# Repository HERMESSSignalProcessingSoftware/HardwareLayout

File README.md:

# HardwareLayout

## To consider for iteration 3.1
- [X] Rename 5V-28V to 5V-noniso
- [X] STAMP labeling
- [X] Northmarking Top and Bottom
- [X] Far fewer power LEDs
- [X] PTH LEDs via ZE05
- [ ] Label LEDs on PCB
- [X] Strip LED resistor network
- [X] LED Renames: LED_FPGA_LOADED(#13), LED_HB_MEMSYNC(#16), LED_HB_MSS(#14), LED_RECORDING(#15)
- [X] Strip 0 and inf valued devices
- [X] Inverting RXSM Connector
- [X] LM4030 for SGR measurement
- [X] VCCINT auf 1.2V
- [X] Bank0 und Bank6 auf 1.2V und connections an Spannung anpassen
- [X] Optocoupling Pullups
- [X] Main Clk for SF2
- [X] Fix broken Flash package
- [X] Replace FT2232D with FT2232H
- [X] (discarded) FTDI 1MOhm beim Oszi?
- [X] (discarded) FTDI Pins 3 42 und Ende R9 an 5V statt 3V3
- [X] (discarded) FTDI SI/WU auf 3V3

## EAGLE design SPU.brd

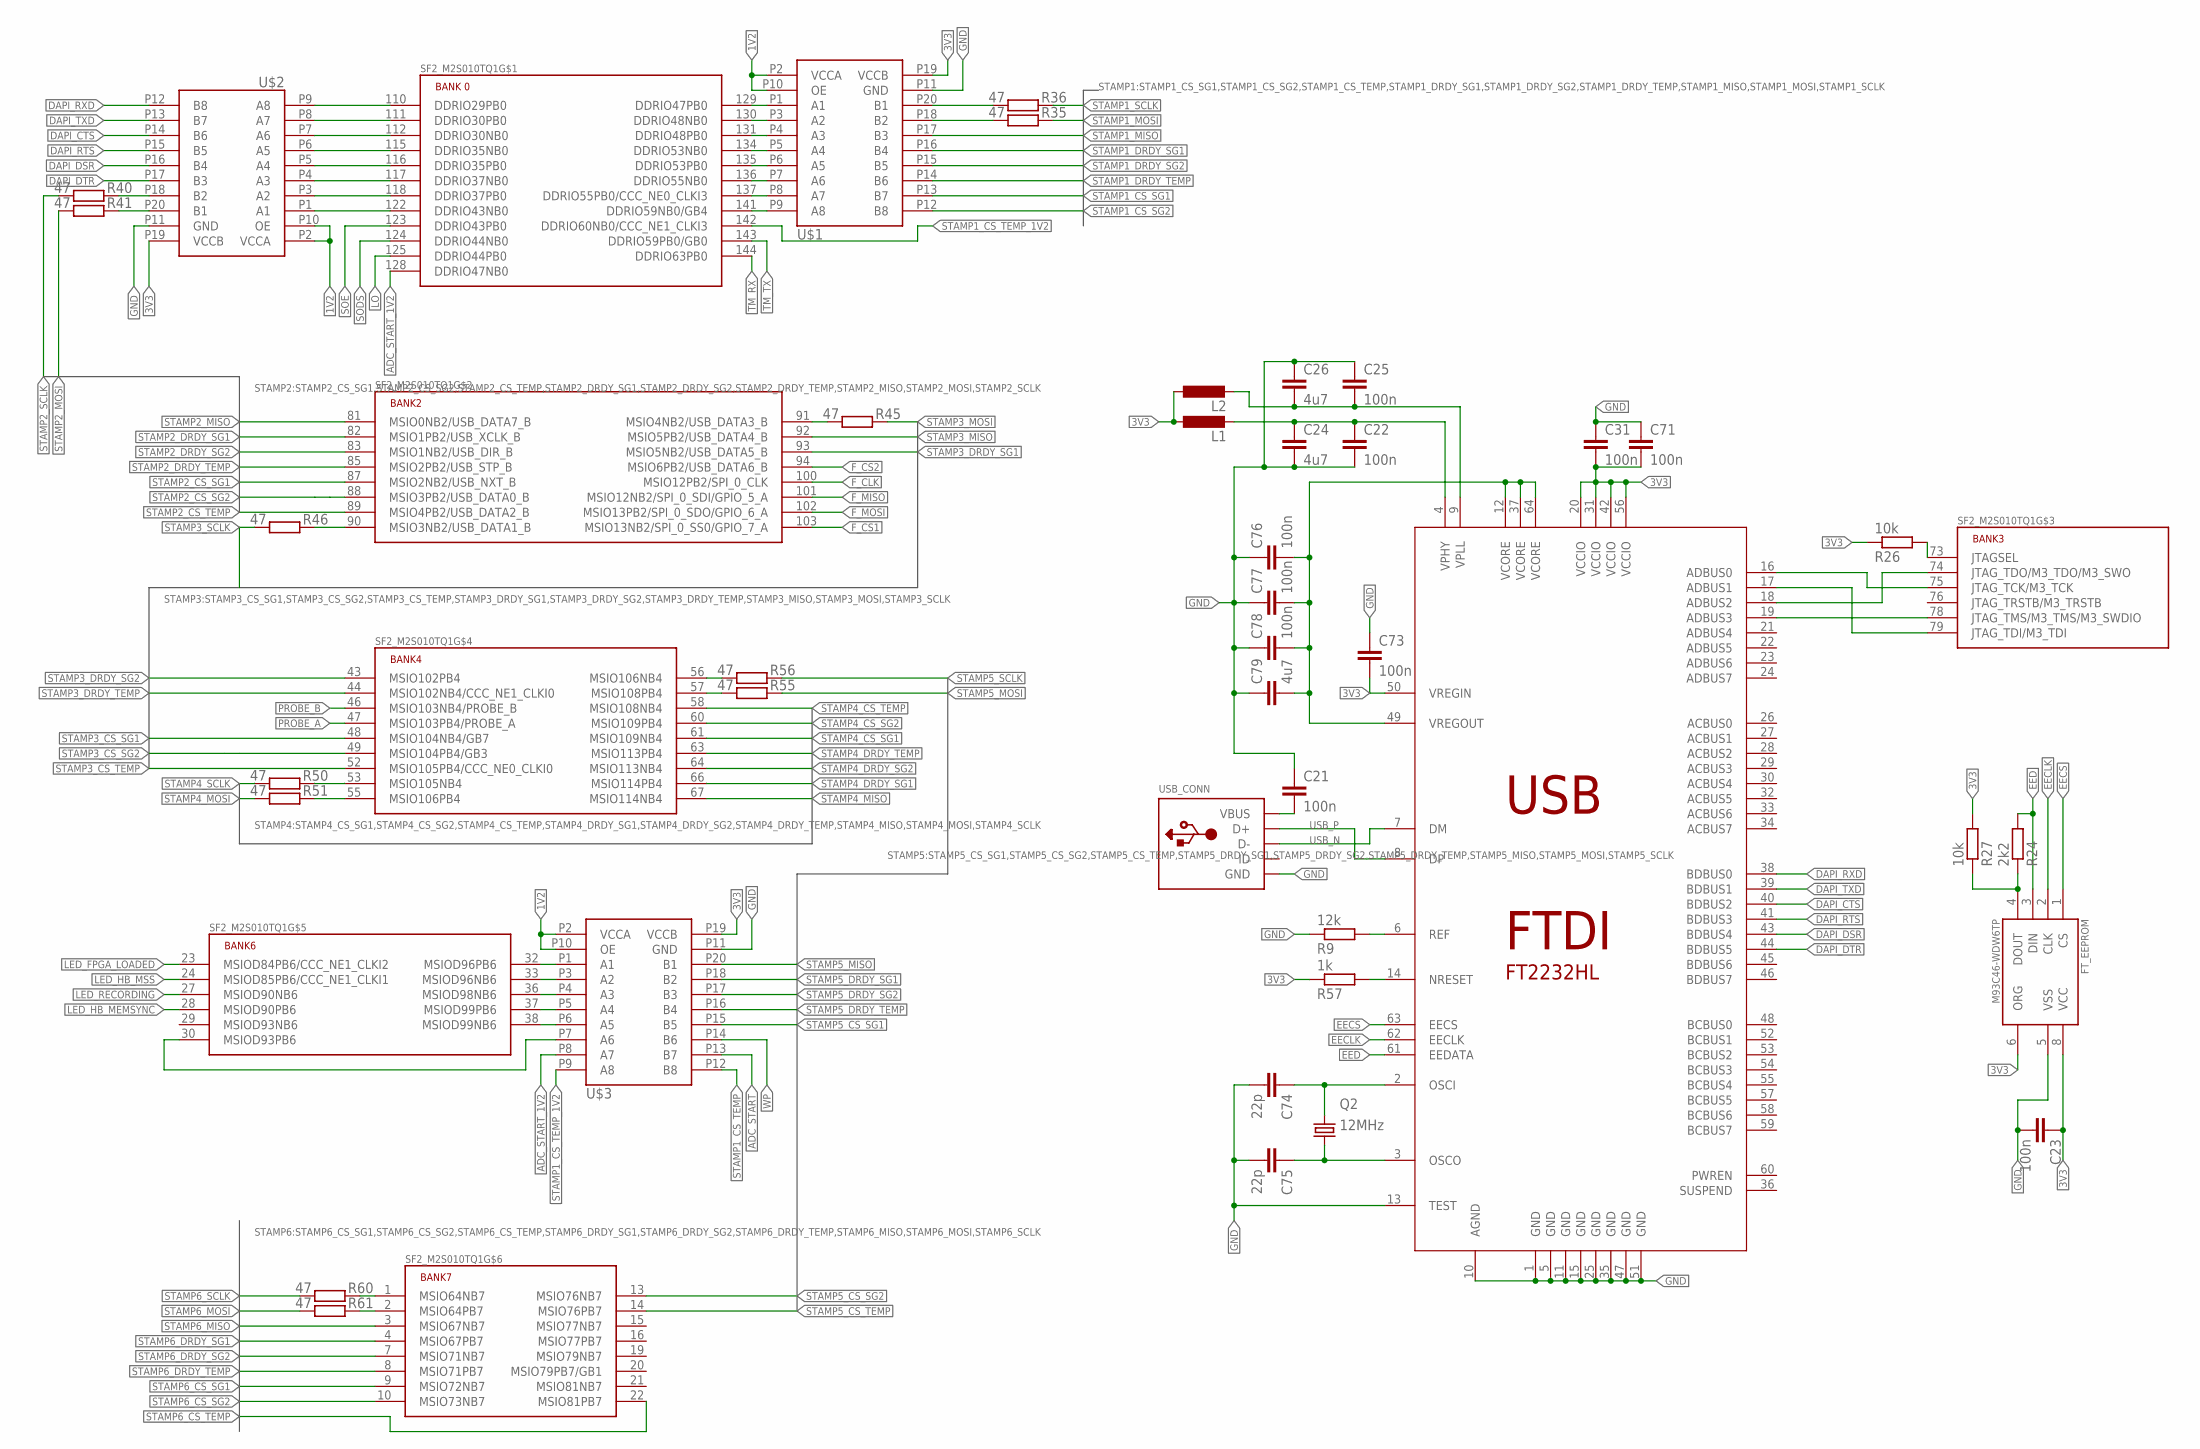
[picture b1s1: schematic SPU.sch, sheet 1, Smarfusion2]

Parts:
C21, C22, C23, C25, C31, C71, C73, C76, C77, C78: 100n; C0805
C24, C26, C79: 4u7; C0805
C74, C75: 22p; C0805
FT_EEPROM: M93C46-WDW6TP; TSSOP-8
L1, L2: L-EUL1812; L1812
Q2: 12MHz; HC49UP
R9: 12k; R0805
R24: 2k2; R0805
R26, R27: 10k; R0805
R35, R36, R40, R41, R45, R46, R50, R51, R55, R56, R60, R61: 47; R0805
R57: 1k; R0805
SF2_M2S010TQ1: SF2_M2S010TQ144; TQFP144
U$1, U$2, U$3: NXB0108PWJ; TSSOP-20
USB: FT2232HL; LQFP64
USB_CONN: USBMINIB; USB-MINIB

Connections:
1V2: U$1.P2 (VCCA), U$1.P10 (OE), U$2.P2 (VCCA), U$2.P10 (OE), U$3.P2 (VCCA), U$3.P10 (OE); also elsewhere on the board
3V3: C23.1, C31.2, C71.2, C73.2, FT_EEPROM.6 (ORG), FT_EEPROM.8 (VCC), L1.1, L2.1, R26.1, R27.2, R57.1, U$1.P19 (VCCB), U$2.P19 (VCCB), U$3.P19 (VCCB), USB.20 (VCCIO), USB.31 (VCCIO), USB.42 (VCCIO), USB.50 (VREGIN), USB.56 (VCCIO); also elsewhere on the board
ADC_START: U$3.P13 (B7); also elsewhere on the board
ADC_START_1V2: SF2_M2S010TQ1.128 (DDRIO47NB0), U$3.P8 (A7)
DAPI_CTS: U$2.P14 (B6), USB.40 (BDBUS2)
DAPI_DSR: U$2.P16 (B4), USB.43 (BDBUS4)
DAPI_DTR: U$2.P17 (B3), USB.44 (BDBUS5)
DAPI_RTS: U$2.P15 (B5), USB.41 (BDBUS3)
DAPI_RXD: U$2.P12 (B8), USB.38 (BDBUS0)
DAPI_TXD: U$2.P13 (B7), USB.39 (BDBUS1)
EECLK: FT_EEPROM.2 (CLK), USB.62 (EECLK)
EECS: FT_EEPROM.1 (CS), USB.63 (EECS)
EED: FT_EEPROM.3 (DIN), R24.2, USB.61 (EEDATA)
F_CLK: SF2_M2S010TQ1.100 (MSIO12PB2/SPI_0_CLK); also elsewhere on the board
F_CS1: SF2_M2S010TQ1.103 (MSIO13NB2/SPI_0_SS0/GPIO_7_A); also elsewhere on the board
F_CS2: SF2_M2S010TQ1.94 (MSIO6PB2/USB_DATA6_B); also elsewhere on the board
F_MISO: SF2_M2S010TQ1.101 (MSIO12NB2/SPI_0_SDI/GPIO_5_A); also elsewhere on the board
F_MOSI: SF2_M2S010TQ1.102 (MSIO13PB2/SPI_0_SDO/GPIO_6_A); also elsewhere on the board
GND: C21.1, C22.2, C23.2, C24.2, C25.1, C26.1, C31.1, C71.1, C73.1, C74.2, C75.2, C76.1, C77.1, C78.1, C79.1, FT_EEPROM.5 (VSS), R9.1, U$1.P11 (GND), U$2.P11 (GND), U$3.P11 (GND), USB.1 (GND), USB.5 (GND), USB.10 (AGND), USB.11 (GND), USB.13 (TEST), USB.15 (GND), USB.25 (GND), USB.35 (GND), USB.47 (GND), USB.51 (GND), USB_CONN.GND; also elsewhere on the board
LED_FPGA_LOADED: SF2_M2S010TQ1.23 (MSIOD84PB6/CCC_NE1_CLKI2); also elsewhere on the board
LED_HB_MEMSYNC: SF2_M2S010TQ1.28 (MSIOD90PB6); also elsewhere on the board
LED_HB_MSS: SF2_M2S010TQ1.24 (MSIOD85PB6/CCC_NE1_CLKI1); also elsewhere on the board
LED_RECORDING: SF2_M2S010TQ1.27 (MSIOD90NB6); also elsewhere on the board
LO: SF2_M2S010TQ1.125 (DDRIO44PB0); also elsewhere on the board
unnamed: R26.2, SF2_M2S010TQ1.73 (JTAGSEL)
unnamed: C74.1, Q2.2, USB.2 (OSCI)
unnamed: SF2_M2S010TQ1.32 (MSIOD96PB6), U$3.P1 (A1)
unnamed: SF2_M2S010TQ1.33 (MSIOD96NB6), U$3.P3 (A2)
unnamed: SF2_M2S010TQ1.36 (MSIOD98NB6), U$3.P4 (A3)
unnamed: C21.2, USB_CONN.VBUS
unnamed: C22.1, C24.1, L1.2, USB.4 (VPHY)
unnamed: R36.2, U$1.P20 (B1)
unnamed: SF2_M2S010TQ1.75 (JTAG_TCK/M3_TCK), USB.16 (ADBUS0)
unnamed: SF2_M2S010TQ1.79 (JTAG_TDI/M3_TDI), USB.17 (ADBUS1)
unnamed: SF2_M2S010TQ1.74 (JTAG_TDO/M3_TDO/M3_SWO), USB.18 (ADBUS2)
unnamed: SF2_M2S010TQ1.78 (JTAG_TMS/M3_TMS/M3_SWDIO), USB.19 (ADBUS3)
unnamed: SF2_M2S010TQ1.37 (MSIOD99PB6), U$3.P5 (A4)
unnamed: FT_EEPROM.4 (DOUT), R24.1, R27.1
unnamed: R35.2, U$1.P18 (B2)
unnamed: SF2_M2S010TQ1.118 (DDRIO37PB0), U$2.P3 (A2)
unnamed: SF2_M2S010TQ1.122 (DDRIO43NB0), U$2.P1 (A1)
unnamed: R40.1, U$2.P18 (B2)
unnamed: SF2_M2S010TQ1.129 (DDRIO47PB0), U$1.P1 (A1)
unnamed: R41.1, U$2.P20 (B1)
unnamed: R46.1, SF2_M2S010TQ1.90 (MSIO3NB2/USB_DATA1_B)
unnamed: R45.2, SF2_M2S010TQ1.91 (MSIO4NB2/USB_DATA3_B)
unnamed: SF2_M2S010TQ1.130 (DDRIO48NB0), U$1.P3 (A2)
unnamed: SF2_M2S010TQ1.131 (DDRIO48PB0), U$1.P4 (A3)
unnamed: SF2_M2S010TQ1.134 (DDRIO53NB0), U$1.P5 (A4)
unnamed: SF2_M2S010TQ1.135 (DDRIO53PB0), U$1.P6 (A5)
unnamed: SF2_M2S010TQ1.136 (DDRIO55NB0), U$1.P7 (A6)
unnamed: SF2_M2S010TQ1.137 (DDRIO55PB0/CCC_NE0_CLKI3), U$1.P8 (A7)
unnamed: SF2_M2S010TQ1.141 (DDRIO59NB0/GB4), U$1.P9 (A8)
unnamed: SF2_M2S010TQ1.38 (MSIOD99NB6), U$3.P6 (A5)
unnamed: SF2_M2S010TQ1.110 (DDRIO29PB0), U$2.P9 (A8)
unnamed: SF2_M2S010TQ1.111 (DDRIO30PB0), U$2.P8 (A7)
unnamed: SF2_M2S010TQ1.112 (DDRIO30NB0), U$2.P7 (A6)
unnamed: SF2_M2S010TQ1.115 (DDRIO35NB0), U$2.P6 (A5)
unnamed: R50.1, SF2_M2S010TQ1.53 (MSIO105NB4)
unnamed: R51.1, SF2_M2S010TQ1.55 (MSIO106PB4)
unnamed: SF2_M2S010TQ1.116 (DDRIO35PB0), U$2.P5 (A4)
unnamed: SF2_M2S010TQ1.117 (DDRIO37NB0), U$2.P4 (A3)
unnamed: SF2_M2S010TQ1.30 (MSIOD93PB6), U$3.P7 (A6)
unnamed: R55.2, SF2_M2S010TQ1.57 (MSIO108PB4)
unnamed: R56.2, SF2_M2S010TQ1.56 (MSIO106NB4)
unnamed: R60.1, SF2_M2S010TQ1.1 (MSIO64NB7)
unnamed: R61.1, SF2_M2S010TQ1.2 (MSIO64PB7)
unnamed: R57.2, USB.14 (NRESET)
unnamed: R9.2, USB.6 (REF)
unnamed: C75.1, Q2.1, USB.3 (OSCO)
unnamed: C76.2, C77.2, C78.2, C79.2, USB.12 (VCORE), USB.37 (VCORE), USB.49 (VREGOUT), USB.64 (VCORE)
unnamed: C25.2, C26.2, L2.2, USB.9 (VPLL)
PROBE_A: SF2_M2S010TQ1.47 (MSIO103PB4/PROBE_A); also elsewhere on the board
PROBE_B: SF2_M2S010TQ1.46 (MSIO103NB4/PROBE_B); also elsewhere on the board
SODS: SF2_M2S010TQ1.124 (DDRIO44NB0); also elsewhere on the board
SOE: SF2_M2S010TQ1.123 (DDRIO43PB0); also elsewhere on the board
STAMP1_CS_SG1: U$1.P13 (B7); also elsewhere on the board
STAMP1_CS_SG2: U$1.P12 (B8); also elsewhere on the board
STAMP1_CS_TEMP: U$3.P12 (B8); also elsewhere on the board
STAMP1_CS_TEMP_1V2: SF2_M2S010TQ1.142 (DDRIO60NB0/CCC_NE1_CLKI3), U$3.P9 (A8)
STAMP1_DRDY_SG1: U$1.P16 (B4); also elsewhere on the board
STAMP1_DRDY_SG2: U$1.P15 (B5); also elsewhere on the board
STAMP1_DRDY_TEMP: U$1.P14 (B6); also elsewhere on the board
STAMP1_MISO: U$1.P17 (B3); also elsewhere on the board
STAMP1_MOSI: R35.1; also elsewhere on the board
STAMP1_SCLK: R36.1; also elsewhere on the board
STAMP2_CS_SG1: SF2_M2S010TQ1.87 (MSIO2NB2/USB_NXT_B); also elsewhere on the board
STAMP2_CS_SG2: SF2_M2S010TQ1.88 (MSIO3PB2/USB_DATA0_B); also elsewhere on the board
STAMP2_CS_TEMP: SF2_M2S010TQ1.89 (MSIO4PB2/USB_DATA2_B); also elsewhere on the board
STAMP2_DRDY_SG1: SF2_M2S010TQ1.82 (MSIO1PB2/USB_XCLK_B); also elsewhere on the board
STAMP2_DRDY_SG2: SF2_M2S010TQ1.83 (MSIO1NB2/USB_DIR_B); also elsewhere on the board
STAMP2_DRDY_TEMP: SF2_M2S010TQ1.85 (MSIO2PB2/USB_STP_B); also elsewhere on the board
STAMP2_MISO: SF2_M2S010TQ1.81 (MSIO0NB2/USB_DATA7_B); also elsewhere on the board
STAMP2_MOSI: R41.2; also elsewhere on the board
STAMP2_SCLK: R40.2; also elsewhere on the board
STAMP3_CS_SG1: SF2_M2S010TQ1.48 (MSIO104NB4/GB7); also elsewhere on the board
STAMP3_CS_SG2: SF2_M2S010TQ1.49 (MSIO104PB4/GB3); also elsewhere on the board
STAMP3_CS_TEMP: SF2_M2S010TQ1.52 (MSIO105PB4/CCC_NE0_CLKI0); also elsewhere on the board
STAMP3_DRDY_SG1: SF2_M2S010TQ1.93 (MSIO5NB2/USB_DATA5_B); also elsewhere on the board
STAMP3_DRDY_SG2: SF2_M2S010TQ1.43 (MSIO102PB4); also elsewhere on the board
STAMP3_DRDY_TEMP: SF2_M2S010TQ1.44 (MSIO102NB4/CCC_NE1_CLKI0); also elsewhere on the board
STAMP3_MISO: SF2_M2S010TQ1.92 (MSIO5PB2/USB_DATA4_B); also elsewhere on the board
STAMP3_MOSI: R45.1; also elsewhere on the board
STAMP3_SCLK: R46.2; also elsewhere on the board
STAMP4_CS_SG1: SF2_M2S010TQ1.61 (MSIO109NB4); also elsewhere on the board
STAMP4_CS_SG2: SF2_M2S010TQ1.60 (MSIO109PB4); also elsewhere on the board
STAMP4_CS_TEMP: SF2_M2S010TQ1.58 (MSIO108NB4); also elsewhere on the board
STAMP4_DRDY_SG1: SF2_M2S010TQ1.66 (MSIO114PB4); also elsewhere on the board
STAMP4_DRDY_SG2: SF2_M2S010TQ1.64 (MSIO113NB4); also elsewhere on the board
STAMP4_DRDY_TEMP: SF2_M2S010TQ1.63 (MSIO113PB4); also elsewhere on the board
STAMP4_MISO: SF2_M2S010TQ1.67 (MSIO114NB4); also elsewhere on the board
STAMP4_MOSI: R51.2; also elsewhere on the board
STAMP4_SCLK: R50.2; also elsewhere on the board
STAMP5_CS_SG1: U$3.P15 (B5); also elsewhere on the board
STAMP5_CS_SG2: SF2_M2S010TQ1.13 (MSIO76NB7); also elsewhere on the board
STAMP5_CS_TEMP: SF2_M2S010TQ1.14 (MSIO76PB7); also elsewhere on the board
STAMP5_DRDY_SG1: U$3.P18 (B2); also elsewhere on the board
STAMP5_DRDY_SG2: U$3.P17 (B3); also elsewhere on the board
STAMP5_DRDY_TEMP: U$3.P16 (B4); also elsewhere on the board
STAMP5_MISO: U$3.P20 (B1); also elsewhere on the board
STAMP5_MOSI: R55.1; also elsewhere on the board
STAMP5_SCLK: R56.1; also elsewhere on the board
STAMP6_CS_SG1: SF2_M2S010TQ1.9 (MSIO72NB7); also elsewhere on the board
STAMP6_CS_SG2: SF2_M2S010TQ1.10 (MSIO73NB7); also elsewhere on the board
STAMP6_CS_TEMP: SF2_M2S010TQ1.22 (MSIO81PB7); also elsewhere on the board
STAMP6_DRDY_SG1: SF2_M2S010TQ1.4 (MSIO67PB7); also elsewhere on the board
STAMP6_DRDY_SG2: SF2_M2S010TQ1.7 (MSIO71NB7); also elsewhere on the board
STAMP6_DRDY_TEMP: SF2_M2S010TQ1.8 (MSIO71PB7); also elsewhere on the board
STAMP6_MISO: SF2_M2S010TQ1.3 (MSIO67NB7); also elsewhere on the board
STAMP6_MOSI: R61.2; also elsewhere on the board
STAMP6_SCLK: R60.2; also elsewhere on the board
TM_RX: SF2_M2S010TQ1.144 (DDRIO63PB0); also elsewhere on the board
TM_TX: SF2_M2S010TQ1.143 (DDRIO59PB0/GB0); also elsewhere on the board
USB_N: USB.7 (DM), USB_CONN.D-
USB_P: USB.8 (DP), USB_CONN.D+
WP: U$3.P14 (B6); also elsewhere on the board

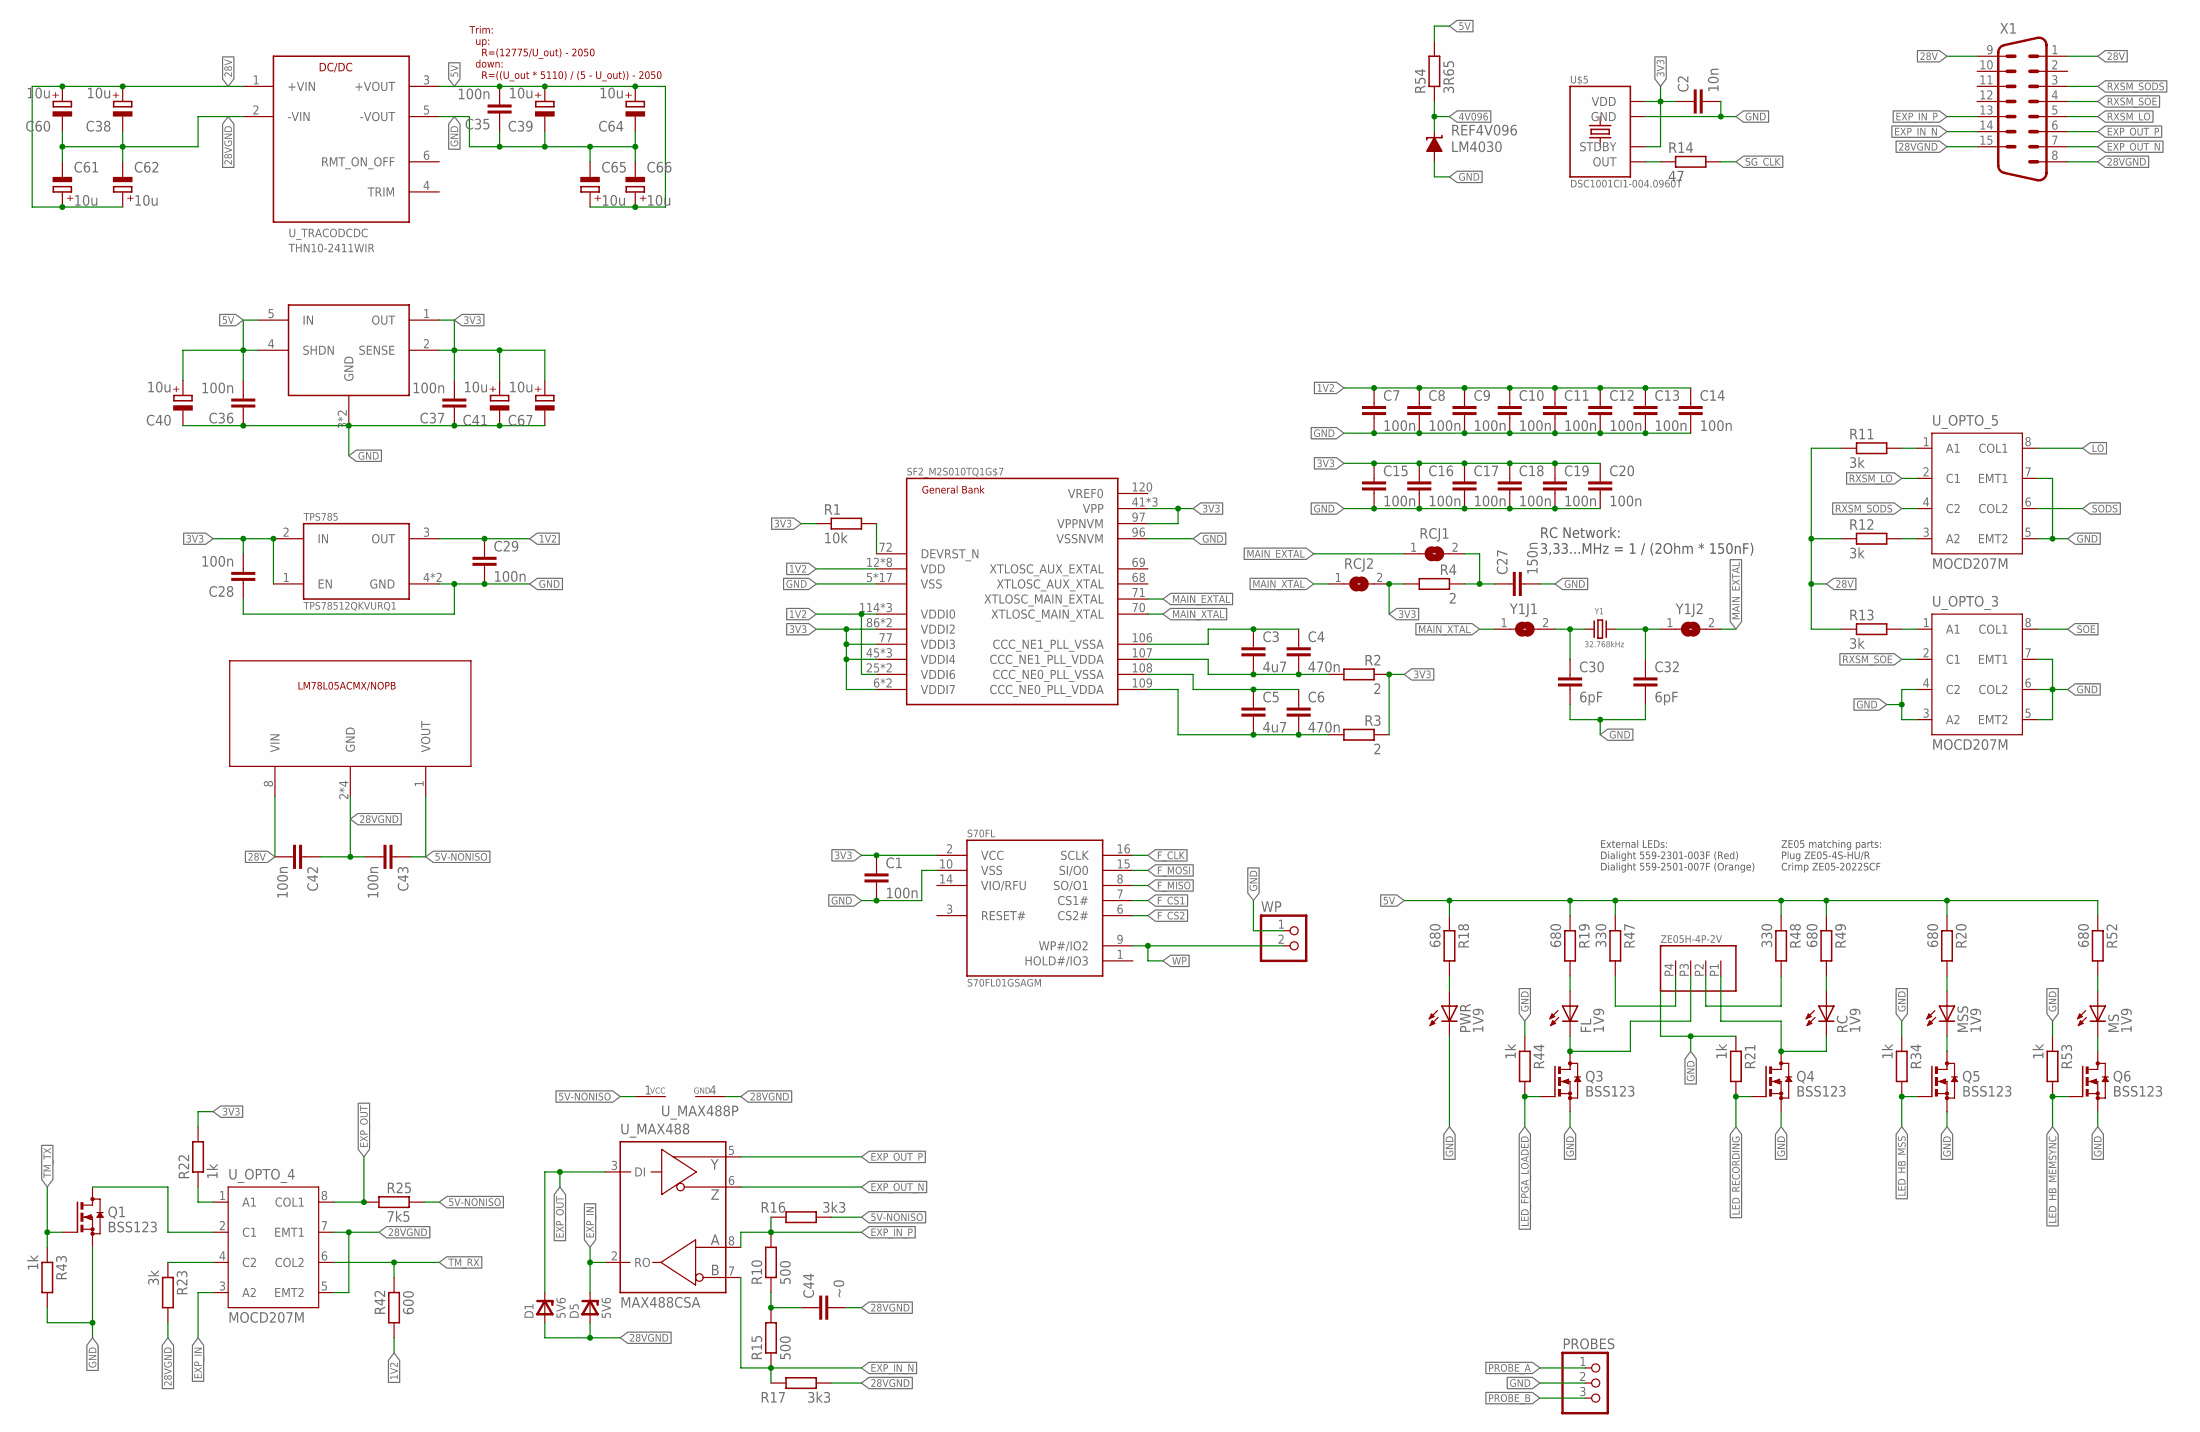
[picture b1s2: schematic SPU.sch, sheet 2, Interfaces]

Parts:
C1, C7, C8, C9, C10, C11, C12, C13, C14, C15, C16, C17, C18, C19, C20, C28, C29, C35, C36, C37, C43: 100n; C0805
C2: 10n; C0805
C3, C5: 4u7; C0805
C4, C6: 470n; C0805
C27: 150n; C0805
C30, C32: 6pF; C0805
C38, C39, C40, C41, C60, C61, C62, C64, C65, C66, C67: 10u; E/7260-38W
C42: 100n; C1206
C44: ~0; C0805
D1, D5: 5V6; DMELF
FL: 1V9; CHIP-LED0805
MS: 1V9; CHIP-LED0805
MSS: 1V9; CHIP-LED0805
PROBES: PSS254_G3
PWR: 1V9; CHIP-LED0805
Q1, Q3, Q4, Q5, Q6: BSS123; SOT23
R1: 10k; R0805
R2, R3, R4: 2; R0805
R10, R15: 500; R0805
R11, R12, R13, R23: 3k; R0805
R14: 47; R0805
R16, R17: 3k3; R0805
R18, R19, R20, R49, R52: 680; R0805
R21, R22, R34, R43, R44, R53: 1k; R0805
R25: 7k5; R0805
R42: 600; R0805
R47, R48: 330; R0805
R54: 3R65; R0805
RC: 1V9; CHIP-LED0805
RCJ1, RCJ2: SJ
REF4V096: LM4030; SOT-23
S70FL: S70FL01GSAGM; SOIC16
SF2_M2S010TQ1: SF2_M2S010TQ144; TQFP144
TPS78512QKVURQ1: TPS785; TO-252-5
U$5: DSC1001CI1-004.0960T; CDFN3225
U_7805: LM78L05ACMX/NOPB; SOIC8
U_LT1528: LT1528; Q5-DD
U_MAX488: MAX488CSA; SO08
U_OPTO_3, U_OPTO_4, U_OPTO_5: MOCD207M; SOIC127P594X363-8N
U_TRACODCDC: THN10-2411WIR; THL_20WI_SERIES
WP: PSS254_G2
X1: M15H
Y1: 32.768kHz; WE-XTAL_IQXC-90
Y1J1, Y1J2: SJ
ZE05H-4P-2V: ZE05-4P-2V; ZE05H-4P-2V

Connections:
1V2: C7.1, C8.1, C9.1, C10.1, C11.1, C12.1, C13.1, C14.1, C29.1, R42.1, SF2_M2S010TQ1.12 (VDD), SF2_M2S010TQ1.25 (VDDI6), SF2_M2S010TQ1.31 (VDD), SF2_M2S010TQ1.35 (VDDI6), SF2_M2S010TQ1.39 (VDD), SF2_M2S010TQ1.50 (VDD), SF2_M2S010TQ1.95 (VDD), SF2_M2S010TQ1.105 (VDD), SF2_M2S010TQ1.114 (VDDI0), SF2_M2S010TQ1.121 (VDD), SF2_M2S010TQ1.127 (VDDI0), SF2_M2S010TQ1.133 (VDD), SF2_M2S010TQ1.138 (VDDI0), TPS78512QKVURQ1.3 (OUT); also elsewhere on the board
3V3: C1.1, C2.1, C15.1, C16.1, C17.1, C18.1, C19.1, C20.1, C28.2, C37.2, C41.+, C67.+, R1.1, R2.1, R3.1, R4.2, R22.2, RCJ2.2, S70FL.2 (VCC), SF2_M2S010TQ1.6 (VDDI7), SF2_M2S010TQ1.17 (VDDI7), SF2_M2S010TQ1.41 (VPP), SF2_M2S010TQ1.45 (VDDI4), SF2_M2S010TQ1.54 (VDDI4), SF2_M2S010TQ1.62 (VDDI4), SF2_M2S010TQ1.77 (VDDI3), SF2_M2S010TQ1.80 (VPP), SF2_M2S010TQ1.86 (VDDI2), SF2_M2S010TQ1.97 (VPPNVM), SF2_M2S010TQ1.99 (VDDI2), SF2_M2S010TQ1.104 (VPP), TPS78512QKVURQ1.1 (EN), TPS78512QKVURQ1.2 (IN), U$5.P1 (STDBY), U$5.P4 (VDD), U_LT1528.1 (OUT), U_LT1528.2 (SENSE); also elsewhere on the board
4V096: R54.1, REF4V096.P4 (C); also elsewhere on the board
5V: C35.2, C36.2, C39.+, C40.+, C64.+, C65.+, C66.+, R18.1, R19.1, R20.1, R47.1, R48.1, R49.1, R52.1, R54.2, U_LT1528.4 (SHDN), U_LT1528.5 (IN), U_TRACODCDC.3 (+VOUT)
5V-NONISO: C43.1, R16.1, R25.2, U_7805.1 (VOUT), U_MAX488.1 (VCC)
28V: C38.+, C42.2, C60.+, C61.+, C62.+, R11.1, R12.1, R13.1, U_7805.8 (VIN), U_TRACODCDC.1 (+VIN), X1.1, X1.9
28VGND: C38.-, C42.1, C43.2, C44.2, C60.-, C61.-, C62.-, D1.A, D5.A, R17.1, R23.2, U_7805.2 (GND), U_7805.3 (GND), U_7805.6 (GND), U_7805.7 (GND), U_MAX488.4 (GND), U_OPTO_4.5 (EMT2), U_OPTO_4.7 (EMT1), U_TRACODCDC.2 (-VIN), X1.8, X1.15
EXP_IN: D5.C, U_MAX488.2 (RO), U_OPTO_4.3 (A2)
EXP_IN_N: R15.1, R17.2, U_MAX488.7 (B), X1.14
EXP_IN_P: R10.2, R16.2, U_MAX488.8 (A), X1.13
EXP_OUT: D1.C, R25.1, U_MAX488.3 (DI), U_OPTO_4.8 (COL1)
EXP_OUT_N: U_MAX488.6 (Z), X1.7
EXP_OUT_P: U_MAX488.5 (Y), X1.6
F_CLK: S70FL.16 (SCLK); also elsewhere on the board
F_CS1: S70FL.7 (CS1#); also elsewhere on the board
F_CS2: S70FL.6 (CS2#); also elsewhere on the board
F_MISO: S70FL.8 (SO/O1); also elsewhere on the board
F_MOSI: S70FL.15 (SI/O0); also elsewhere on the board
GND: C1.2, C2.2, C7.2, C8.2, C9.2, C10.2, C11.2, C12.2, C13.2, C14.2, C15.2, C16.2, C17.2, C18.2, C19.2, C20.2, C27.2, C28.1, C29.2, C30.2, C32.2, C35.1, C36.1, C37.1, C39.-, C40.-, C41.-, C64.-, C65.-, C66.-, C67.-, PROBES.2, PWR.C, Q1.2 (S), Q3.2 (S), Q4.2 (S), Q5.2 (S), Q6.2 (S), R21.1, R34.1, R43.2, R44.1, R53.1, REF4V096.P5 (A), S70FL.10 (VSS), SF2_M2S010TQ1.5 (VSS), SF2_M2S010TQ1.11 (VSS), SF2_M2S010TQ1.18 (VSS), SF2_M2S010TQ1.26 (VSS), SF2_M2S010TQ1.34 (VSS), SF2_M2S010TQ1.40 (VSS), SF2_M2S010TQ1.42 (VSS), SF2_M2S010TQ1.51 (VSS), SF2_M2S010TQ1.59 (VSS), SF2_M2S010TQ1.65 (VSS), SF2_M2S010TQ1.84 (VSS), SF2_M2S010TQ1.96 (VSSNVM), SF2_M2S010TQ1.98 (VSS), SF2_M2S010TQ1.113 (VSS), SF2_M2S010TQ1.119 (VSS), SF2_M2S010TQ1.126 (VSS), SF2_M2S010TQ1.132 (VSS), SF2_M2S010TQ1.139 (VSS), TPS78512QKVURQ1.4 (GND), TPS78512QKVURQ1.5 (GND), U$5.P2 (GND), U_LT1528.3 (GND), U_LT1528.6 (GND), U_OPTO_3.3 (A2), U_OPTO_3.4 (C2), U_OPTO_3.5 (EMT2), U_OPTO_3.6 (COL2), U_OPTO_3.7 (EMT1), U_OPTO_5.5 (EMT2), U_OPTO_5.7 (EMT1), U_TRACODCDC.5 (-VOUT), WP.1, ZE05H-4P-2V.P5, ZE05H-4P-2V.P6; also elsewhere on the board
LED_FPGA_LOADED: Q3.1 (G), R44.2; also elsewhere on the board
LED_HB_MEMSYNC: Q6.1 (G), R53.2; also elsewhere on the board
LED_HB_MSS: Q5.1 (G), R34.2; also elsewhere on the board
LED_RECORDING: Q4.1 (G), R21.2; also elsewhere on the board
LO: U_OPTO_5.8 (COL1); also elsewhere on the board
MAIN_EXTAL: RCJ1.1, SF2_M2S010TQ1.71 (XTLOSC_MAIN_EXTAL), Y1J2.2
MAIN_XTAL: RCJ2.1, SF2_M2S010TQ1.70 (XTLOSC_MAIN_XTAL), Y1J1.1
unnamed: C44.1, R10.1, R15.2
unnamed: R1.2, SF2_M2S010TQ1.72 (DEVRST_N)
unnamed: R23.1, U_OPTO_4.4 (C2)
unnamed: C3.1, C4.1, SF2_M2S010TQ1.106 (CCC_NE1_PLL_VSSA)
unnamed: C3.2, C4.2, R2.2, SF2_M2S010TQ1.107 (CCC_NE1_PLL_VDDA)
unnamed: C5.2, C6.2, R3.2, SF2_M2S010TQ1.109 (CCC_NE0_PLL_VDDA)
unnamed: C5.1, C6.1, SF2_M2S010TQ1.108 (CCC_NE0_PLL_VSSA)
unnamed: C30.1, Y1.1, Y1J1.2
unnamed: R13.2, U_OPTO_3.1 (A1)
unnamed: R12.2, U_OPTO_5.3 (A2)
unnamed: R11.2, U_OPTO_5.1 (A1)
unnamed: R22.1, U_OPTO_4.1 (A1)
unnamed: R14.1, U$5.P3 (OUT)
unnamed: PWR.A, R18.2
unnamed: MS.C, Q6.3 (D)
unnamed: MSS.C, Q5.3 (D)
unnamed: Q1.3 (D), U_OPTO_4.2 (C1)
unnamed: FL.A, R19.2
unnamed: MSS.A, R20.2
unnamed: C32.1, Y1.2, Y1J2.1
unnamed: MS.A, R52.2
unnamed: R49.2, RC.A
unnamed: R47.2, ZE05H-4P-2V.P4
unnamed: Q4.3 (D), RC.C, ZE05H-4P-2V.P1
unnamed: R48.2, ZE05H-4P-2V.P2
unnamed: FL.C, Q3.3 (D), ZE05H-4P-2V.P3
NET_U: C27.1, R4.1, RCJ1.2
PROBE_A: PROBES.1; also elsewhere on the board
PROBE_B: PROBES.3; also elsewhere on the board
RXSM_LO: U_OPTO_5.2 (C1), X1.5
RXSM_SODS: U_OPTO_5.4 (C2), X1.3
RXSM_SOE: U_OPTO_3.2 (C1), X1.4
SG_CLK: R14.2; also elsewhere on the board
SODS: U_OPTO_5.6 (COL2); also elsewhere on the board
SOE: U_OPTO_3.8 (COL1); also elsewhere on the board
TM_RX: R42.2, U_OPTO_4.6 (COL2); also elsewhere on the board
TM_TX: Q1.1 (G), R43.1; also elsewhere on the board
WP: S70FL.9 (WP#/IO2), WP.2; also elsewhere on the board

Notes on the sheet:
LM78L05ACMX/NOPB
Trim: up: R=(12775/U_out) - 2050 down: R=((U_out * 5110) / (5 - U_out)) - 2050
External LEDs: Dialight 559-2301-003F (Red) Dialight 559-2501-007F (Orange)
ZE05 matching parts: Plug ZE05-4S-HU/R Crimp ZE05-2022SCF
RC Network: 3,33...MHz = 1 / (2Ohm * 150nF)

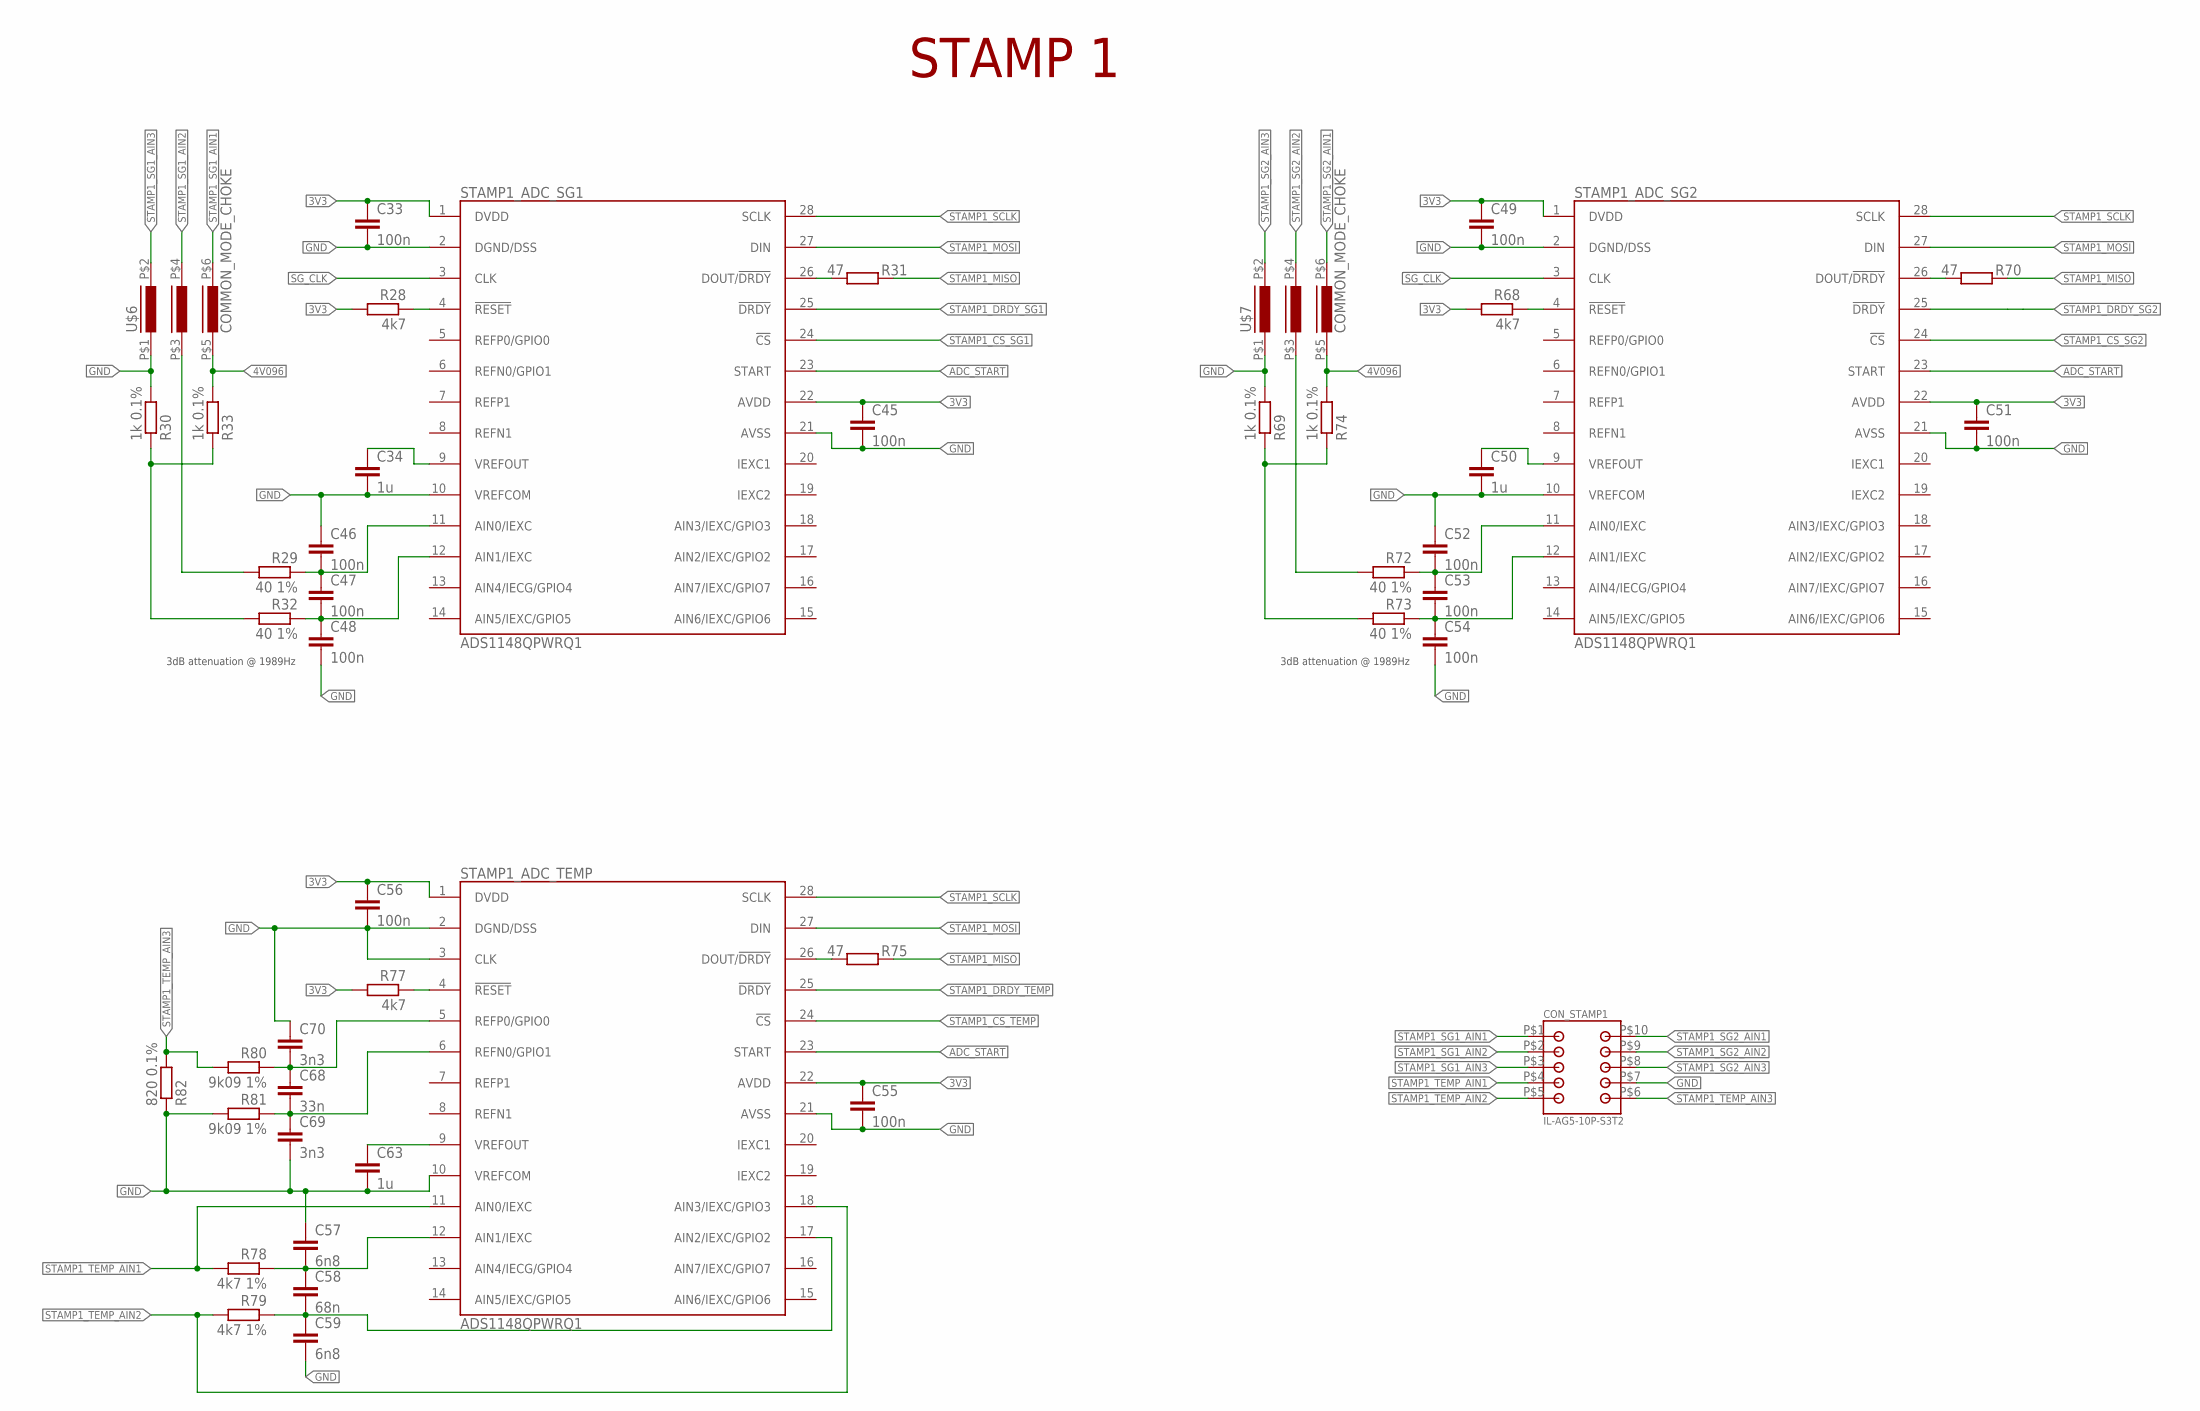
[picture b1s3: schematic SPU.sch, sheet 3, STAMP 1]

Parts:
C33, C45, C46, C47, C48, C49, C51, C52, C53, C54, C55, C56: 100n; C0805
C34, C50, C63: 1u; C0805
C57, C59: 6n8; C0805
C58: 68n; C0805
C68: 33n; C0805
C69, C70: 3n3; C0805
CON_STAMP1: IL-AG5-10P-S3T2
R28, R68, R77: 4k7; R0805
R29, R32, R72, R73: 40 1%; R0805
R30, R33, R69, R74: 1k 0.1%; R0805
R31, R70, R75: 47; R0805
R78, R79: 4k7 1%; R0805
R80, R81: 9k09 1%; R0805
R82: 820 0.1%; R0805
STAMP1_ADC_SG1, STAMP1_ADC_SG2, STAMP1_ADC_TEMP: ADS1148QPWRQ1; TSSOP28
U$6, U$7: COMMON_MODE_CHOKE

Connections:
3V3: C33.1, C45.1, C49.1, C51.1, C55.1, C56.1, R28.2, R68.2, R77.2, STAMP1_ADC_SG1.1 (DVDD), STAMP1_ADC_SG1.22 (AVDD), STAMP1_ADC_SG2.1 (DVDD), STAMP1_ADC_SG2.22 (AVDD), STAMP1_ADC_TEMP.1 (DVDD), STAMP1_ADC_TEMP.22 (AVDD); also elsewhere on the board
4V096: R33.2, R74.2, U$6.P$5 (5), U$7.P$5 (5); also elsewhere on the board
ADC_START: STAMP1_ADC_SG1.23 (START), STAMP1_ADC_SG2.23 (START), STAMP1_ADC_TEMP.23 (START); also elsewhere on the board
GND: C33.2, C34.2, C45.2, C46.1, C48.2, C49.2, C50.2, C51.2, C52.1, C54.2, C55.2, C56.2, C57.1, C59.2, C63.2, C69.2, C70.1, CON_STAMP1.P$7, R30.2, R69.2, R81.2, R82.1, STAMP1_ADC_SG1.2 (DGND/DSS), STAMP1_ADC_SG1.10 (VREFCOM), STAMP1_ADC_SG1.21 (AVSS), STAMP1_ADC_SG2.2 (DGND/DSS), STAMP1_ADC_SG2.10 (VREFCOM), STAMP1_ADC_SG2.21 (AVSS), STAMP1_ADC_TEMP.2 (DGND/DSS), STAMP1_ADC_TEMP.3 (CLK), STAMP1_ADC_TEMP.10 (VREFCOM), STAMP1_ADC_TEMP.21 (AVSS), U$6.P$1 (1), U$7.P$1 (1); also elsewhere on the board
unnamed: C34.1, STAMP1_ADC_SG1.9 (VREFOUT)
unnamed: R68.1, STAMP1_ADC_SG2.4 (!RESET)
unnamed: R28.1, STAMP1_ADC_SG1.4 (!RESET)
unnamed: R31.2, STAMP1_ADC_SG1.26 (DOUT/!DRDY)
unnamed: C46.2, C47.1, R29.1, STAMP1_ADC_SG1.11 (AIN0/IEXC)
unnamed: C47.2, C48.1, R32.1, STAMP1_ADC_SG1.12 (AIN1/IEXC)
unnamed: C50.1, STAMP1_ADC_SG2.9 (VREFOUT)
unnamed: R70.2, STAMP1_ADC_SG2.26 (DOUT/!DRDY)
unnamed: C52.2, C53.1, R72.1, STAMP1_ADC_SG2.11 (AIN0/IEXC)
unnamed: C53.2, C54.1, R73.1, STAMP1_ADC_SG2.12 (AIN1/IEXC)
unnamed: R30.1, R32.2, R33.1
unnamed: R69.1, R73.2, R74.1
unnamed: R29.2, U$6.P$3 (3)
unnamed: R72.2, U$7.P$3 (3)
unnamed: R75.2, STAMP1_ADC_TEMP.26 (DOUT/!DRDY)
unnamed: R77.1, STAMP1_ADC_TEMP.4 (!RESET)
unnamed: C57.2, C58.1, R78.1, STAMP1_ADC_TEMP.12 (AIN1/IEXC)
unnamed: C58.2, C59.1, R79.1, STAMP1_ADC_TEMP.17 (AIN2/IEXC/GPIO2)
unnamed: C63.1, STAMP1_ADC_TEMP.9 (VREFOUT)
unnamed: C68.2, C69.1, R81.1, STAMP1_ADC_TEMP.6 (REFN0/GPIO1)
unnamed: C68.1, C70.2, R80.1, STAMP1_ADC_TEMP.5 (REFP0/GPIO0)
SG_CLK: STAMP1_ADC_SG1.3 (CLK), STAMP1_ADC_SG2.3 (CLK); also elsewhere on the board
STAMP1_CS_SG1: STAMP1_ADC_SG1.24 (!CS); also elsewhere on the board
STAMP1_CS_SG2: STAMP1_ADC_SG2.24 (!CS); also elsewhere on the board
STAMP1_CS_TEMP: STAMP1_ADC_TEMP.24 (!CS); also elsewhere on the board
STAMP1_DRDY_SG1: STAMP1_ADC_SG1.25 (!DRDY); also elsewhere on the board
STAMP1_DRDY_SG2: STAMP1_ADC_SG2.25 (!DRDY); also elsewhere on the board
STAMP1_DRDY_TEMP: STAMP1_ADC_TEMP.25 (!DRDY); also elsewhere on the board
STAMP1_MISO: R31.1, R70.1, R75.1; also elsewhere on the board
STAMP1_MOSI: STAMP1_ADC_SG1.27 (DIN), STAMP1_ADC_SG2.27 (DIN), STAMP1_ADC_TEMP.27 (DIN); also elsewhere on the board
STAMP1_SCLK: STAMP1_ADC_SG1.28 (SCLK), STAMP1_ADC_SG2.28 (SCLK), STAMP1_ADC_TEMP.28 (SCLK); also elsewhere on the board
STAMP1_SG1_AIN1: CON_STAMP1.P$1, U$6.P$6 (6)
STAMP1_SG1_AIN2: CON_STAMP1.P$2, U$6.P$4 (4)
STAMP1_SG1_AIN3: CON_STAMP1.P$3, U$6.P$2 (2)
STAMP1_SG2_AIN1: CON_STAMP1.P$10, U$7.P$6 (6)
STAMP1_SG2_AIN2: CON_STAMP1.P$9, U$7.P$4 (4)
STAMP1_SG2_AIN3: CON_STAMP1.P$8, U$7.P$2 (2)
STAMP1_TEMP_AIN1: CON_STAMP1.P$4, R78.2, STAMP1_ADC_TEMP.11 (AIN0/IEXC)
STAMP1_TEMP_AIN2: CON_STAMP1.P$5, R79.2, STAMP1_ADC_TEMP.18 (AIN3/IEXC/GPIO3)
STAMP1_TEMP_AIN3: CON_STAMP1.P$6, R80.2, R82.2

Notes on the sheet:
3dB attenuation @ 1989Hz
STAMP 1

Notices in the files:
parts and their libraries:
m-pad-2.1: License : GNU General Public License version 2 (see bottom)
aSparkFun: Licensing: CC v3.0 Share-Alike You are welcome to use this library for commercial purposes.
Eagle_WE-XTAL: Copyright: Würth Elektronik
dframes: Copyright (C) 2004, Bob Starr (bobstarr@mindspring.com)
